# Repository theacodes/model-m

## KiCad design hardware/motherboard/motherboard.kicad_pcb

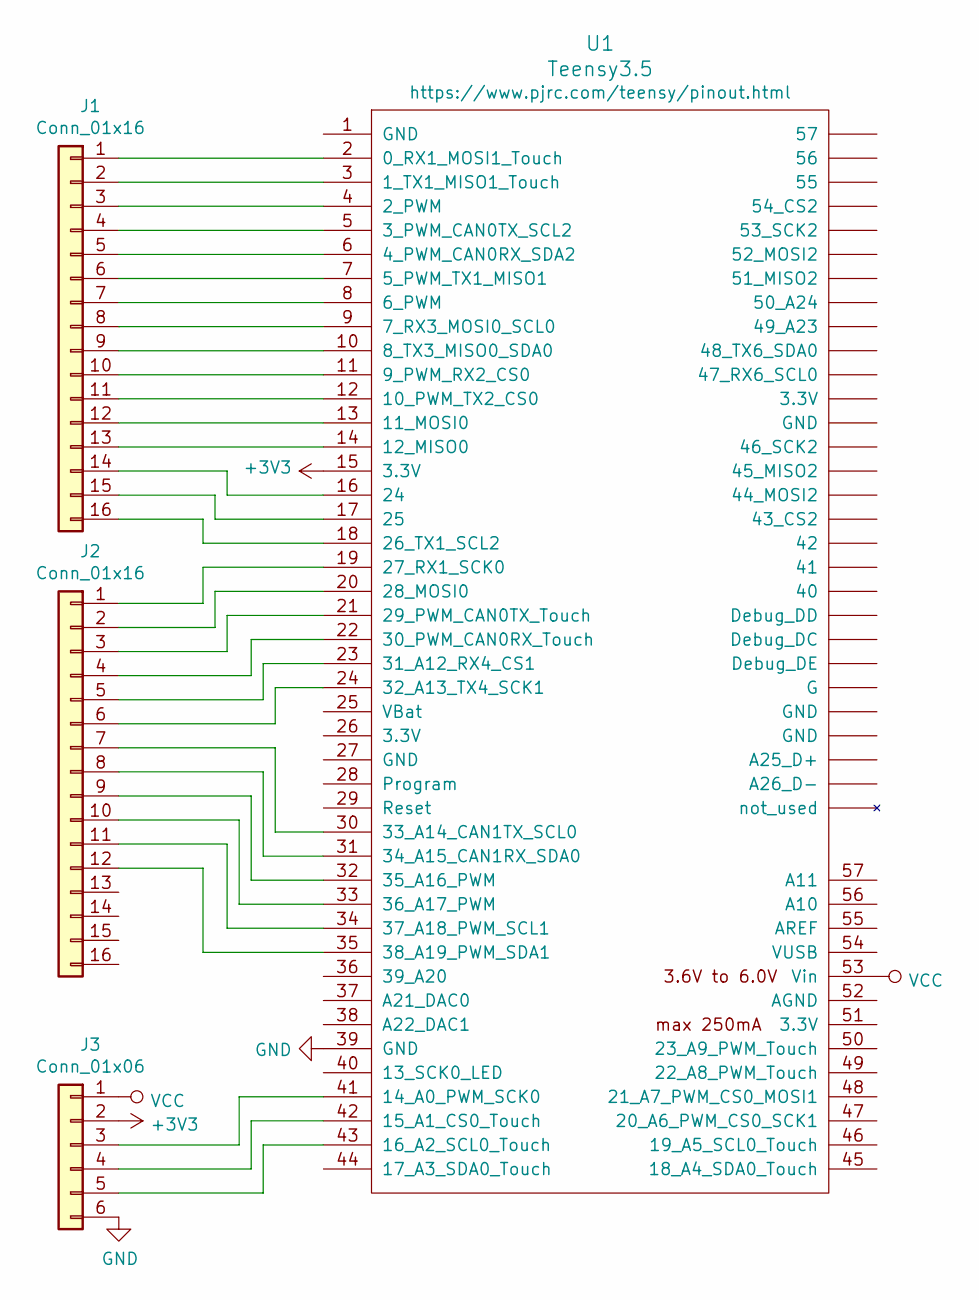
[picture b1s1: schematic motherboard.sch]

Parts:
J1, J2: Conn_01x16; 1X16_LONGPADS
J3: Conn_01x06; 1X06_LONGPADS
U1: Teensy3.5; Teensy35_36

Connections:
+3V3: J3.2, U1.15 (3.3V)
GND: J3.6, U1.39 (GND)
unnamed: J1.1, U1.2 (0_RX1_MOSI1_Touch)
unnamed: J1.2, U1.3 (1_TX1_MISO1_Touch)
unnamed: J1.3, U1.4 (2_PWM)
unnamed: J1.4, U1.5 (3_PWM_CAN0TX_SCL2)
unnamed: J1.5, U1.6 (4_PWM_CAN0RX_SDA2)
unnamed: J1.6, U1.7 (5_PWM_TX1_MISO1)
unnamed: J1.7, U1.8 (6_PWM)
unnamed: J1.8, U1.9 (7_RX3_MOSI0_SCL0)
unnamed: J1.9, U1.10 (8_TX3_MISO0_SDA0)
unnamed: J1.10, U1.11 (9_PWM_RX2_CS0)
unnamed: J1.11, U1.12 (10_PWM_TX2_CS0)
unnamed: J1.12, U1.13 (11_MOSI0)
unnamed: J1.13, U1.14 (12_MISO0)
unnamed: J1.14, U1.16 (24)
unnamed: J1.15, U1.17 (25)
unnamed: J1.16, U1.18 (26_TX1_SCL2)
unnamed: J2.1, U1.19 (27_RX1_SCK0)
unnamed: J2.2, U1.20 (28_MOSI0)
unnamed: J2.3, U1.21 (29_PWM_CAN0TX_Touch)
unnamed: J2.4, U1.22 (30_PWM_CAN0RX_Touch)
unnamed: J2.5, U1.23 (31_A12_RX4_CS1)
unnamed: J2.6, U1.24 (32_A13_TX4_SCK1)
unnamed: J2.7, U1.30 (33_A14_CAN1TX_SCL0)
unnamed: J2.8, U1.31 (34_A15_CAN1RX_SDA0)
unnamed: J2.9, U1.32 (35_A16_PWM)
unnamed: J2.10, U1.33 (36_A17_PWM)
unnamed: J2.11, U1.34 (37_A18_PWM_SCL1)
unnamed: J2.12, U1.35 (38_A19_PWM_SDA1)
unnamed: J3.3, U1.41 (14_A0_PWM_SCK0)
unnamed: J3.4, U1.42 (15_A1_CS0_Touch)
unnamed: J3.5, U1.43 (16_A2_SCL0_Touch)
VCC: J3.1, U1.53 (Vin)

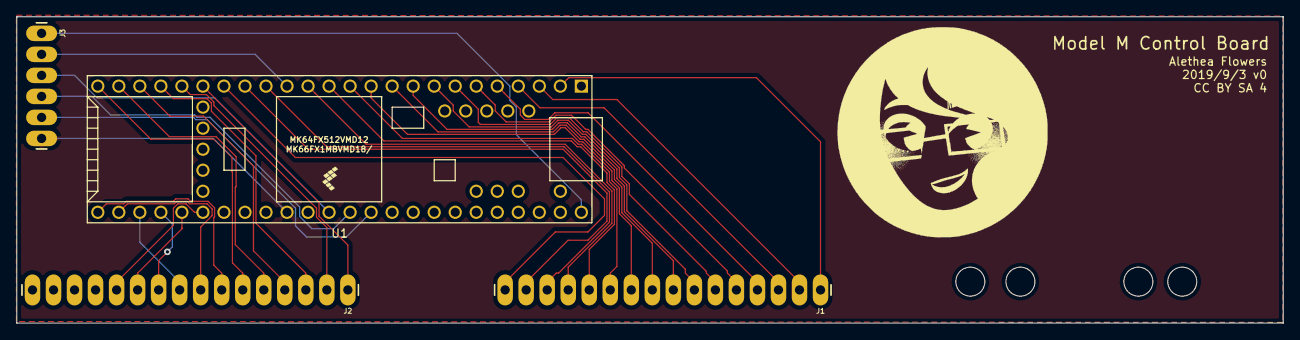
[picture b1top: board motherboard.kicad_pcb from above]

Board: 2 copper layers, 153.0 x 37.0 mm, 5 parts (0 on the bottom side), 34 nets.

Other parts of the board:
e: MountingHole_3.5mm

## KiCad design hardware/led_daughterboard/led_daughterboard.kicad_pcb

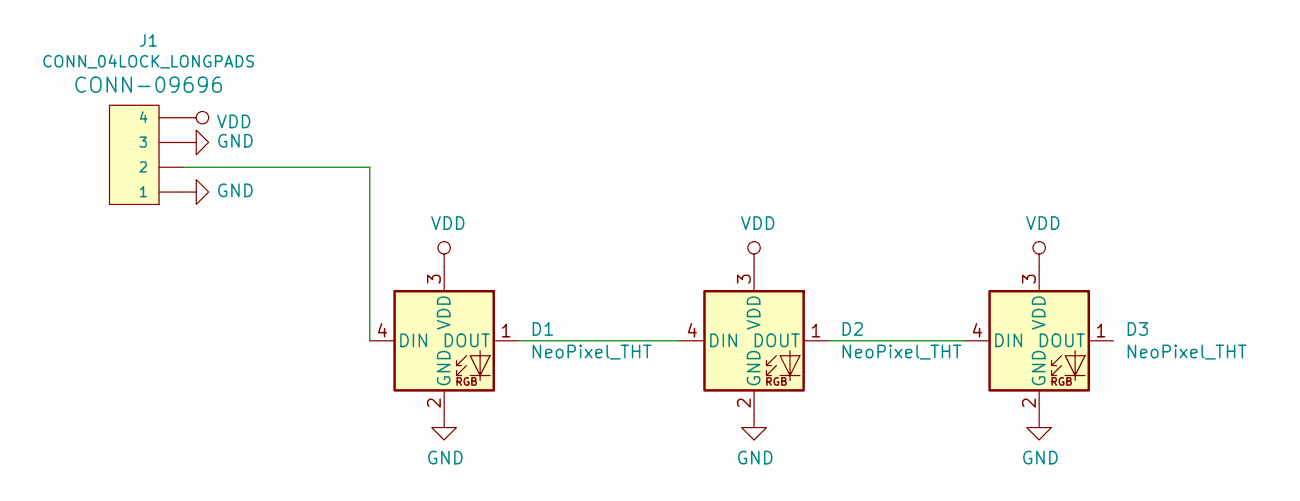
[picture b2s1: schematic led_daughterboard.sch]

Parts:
D1, D2, D3: NeoPixel_THT; LED_D5.0mm-4_RGB
J1: CONN_04LOCK_LONGPADS; 1X04_LOCK_LONGPADS

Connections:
GND: D1.2 (GND), D2.2 (GND), D3.2 (GND), J1.1, J1.3
unnamed: D1.1 (DOUT), D2.4 (DIN)
unnamed: D1.4 (DIN), J1.2
unnamed: D2.1 (DOUT), D3.4 (DIN)
VDD: D1.3 (VDD), D2.3 (VDD), D3.3 (VDD), J1.4

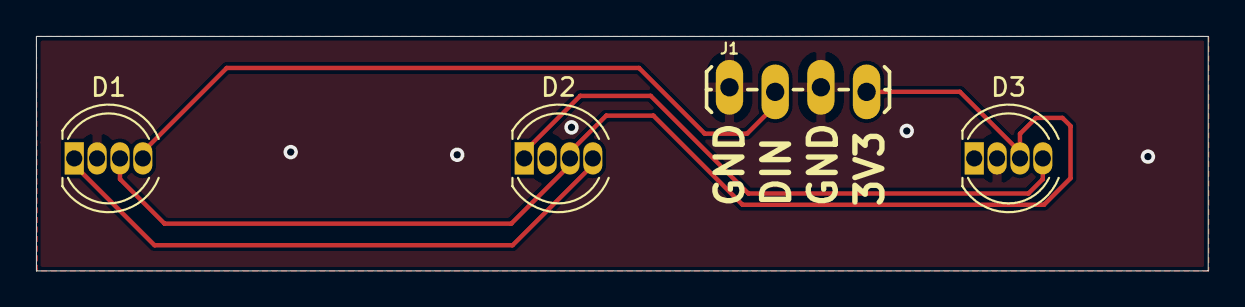
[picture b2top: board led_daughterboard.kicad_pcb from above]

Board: 2 copper layers, 65.1 x 13.0 mm, 4 parts (0 on the bottom side), 5 nets.

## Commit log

2019-12-22 Instructions to install Adafruit NeoPixel Library (#1)
2020-02-12 clean up errant whitespace (#2)

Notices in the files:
hardware/led_daughterboard/led_daughterboard.kicad_pcb:
CC-BY-SA 4.0
hardware/motherboard/motherboard.kicad_pcb:
CC BY SA 4
